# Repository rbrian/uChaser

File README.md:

# uFollow
Follow the project here: https://hackaday.io/project/190427-uchaser-ultrasonic-following-control-system

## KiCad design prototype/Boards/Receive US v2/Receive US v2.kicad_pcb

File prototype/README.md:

Prototype receiver and transmitter:

Transmitter firmware Todo list:
- [ ] Refactor to align with receiver code structure
- [x] JSON storage for settings
- [x] Automatic pairing with receiver (initiated by receiver)
- [ ] Add webserver, wifi access point
- [ ] Create a configuration page
- [ ] Implement the LED
- [ ] Remove the display or make it optional (use the qwiic connector)
- [ ] Get rid of all the serial.print commands everwhere
- [ ] Enable/disable, to stop the receiver from outputting

Receiver firmware todo list:
- [x] Add webserver, wifi access point
- [x] JSON storage for settings
- [x] Automatic pairing - one button
- [ ] Create a configuration page
- [ ] Make the LED do more interesting stuff
- [ ] Remove the display or make it optional (use the qwiic connector)
- [ ] Get rid of all the serial.print commands everwhere
- [ ] Outputs: UART, PWM, I2C, SPI, etc?
- [ ] Enable/Disable from transmitter
- [ ] Improve the averaging/smoothing.  Throw out bogus values
- [ ] Handle signal loss or line of sight issues
- [ ] Measure the jitter in ESP-NOW timing

Hardware wish list:
- [x] Next revision of receiver board
- [ ] Receiver mcu board: clearly mark TX and RX as IN or OUT
- [ ] Receiver mcu board: SCL and SDA are swapped
- [ ] Receiver mcu board: replace the diode with a mosfet
- [ ] Power supply for transmitter suitable for battery operation
- [ ] Try out switching between multiple tx transcievers for better angle tolerance
- [ ] Figure out which pins to expose

There are two main layers - RF and Ultrasonic.  The RF layer is wifi, using the ESP-NOW protocol.  The transmitting device sends a packet and the receiving one receives it (duh).

We are using the ESP32-S3 devkit board: https://docs.espressif.com/projects/esp-idf/en/latest/esp32s3/hw-reference/esp32s3/user-guide-devkitc-1.html
and this adafruit OLED display: https://www.adafruit.com/product/4650

For now the circuits are identical, only the code is different.

RMT peripheral documentation (for generating waveforms/pulse sequences)
https://docs.espressif.com/projects/esp-idf/en/latest/esp32s3/api-reference/peripherals/rmt.html

For the revision 1 receiver:
- The squelch pin mutes the data output while it is high
- The data pin is normally low, transitions to high when a ping is received
- The squelch pin also resets the one-shot circuit, so:
1. Keep the squelch pin high normally
2. When a wifi packet is received, set that pin to low
3. When the data pin goes high (interrupt pin), log that timestamp and reset the squelch pin to high again
4. if too much time passes without the data pin changing, set the squelch high and wait for the next packet
5. Repeat forever

Component notes:
ESP32-S3 (this is the lowest model): https://www.lcsc.com/product-detail/WiFi-Modules_Espressif-Systems-ESP32-S3-WROOM-1-N4_C2913197.html

USB-UART CH340c: https://www.lcsc.com/product-detail/USB-ICs_WCH-Jiangsu-Qin-Heng-CH340C_C84681.html

DC-DC Module: https://www.lcsc.com/product-detail/Power-Modules_DEXU-Electronics-K7803M-1000R3_C2916516.html

almost 12 inch cable with JST XH connector: https://www.lcsc.com/product-detail/Dupont-Cable-Terminal-Block-Cable-Electronic-Cable_DEALON-LNN254-100724-300-4P_C5160861.html

Same cable but double ended: https://www.lcsc.com/product-detail/Dupont-Cable-Terminal-Block-Cable-Electronic-Cable_DEALON-LDS254-100724-300-4P_C5160865.html

XH vertical board connector:
- white: https://www.lcsc.com/product-detail/Wire-To-Board-Wire-To-Wire-Connector_HCTL-XH-4A_C2908602.html
- black: https://www.lcsc.com/product-detail/Wire-To-Board-Wire-To-Wire-Connector_HCTL-XH-4A-B_C2979570.html
- red: https://www.lcsc.com/product-detail/Wire-To-Board-Wire-To-Wire-Connector_HCTL-XH-4A-R_C2979568.html
- blue: https://www.lcsc.com/product-detail/Wire-To-Board-Wire-To-Wire-Connector_HCTL-XH-4A-L_C2979569.html

XH horizontal board connector: https://www.lcsc.com/product-detail/Wire-To-Board-Wire-To-Wire-Connector_BOOMELE-Boom-Precision-Elec-XH-4AW_C21273.html

Qwiic
- Real JST: https://www.lcsc.com/product-detail/Wire-To-Board-Wire-To-Wire-Connector_JST-Sales-America-BM04B-SRSS-TB-LF-SN_C160390.html
- Cheap clone: https://www.lcsc.com/product-detail/Wire-To-Board-Wire-To-Wire-Connector_JUSHUO-AFC10-S04QCA-00_C2764183.html

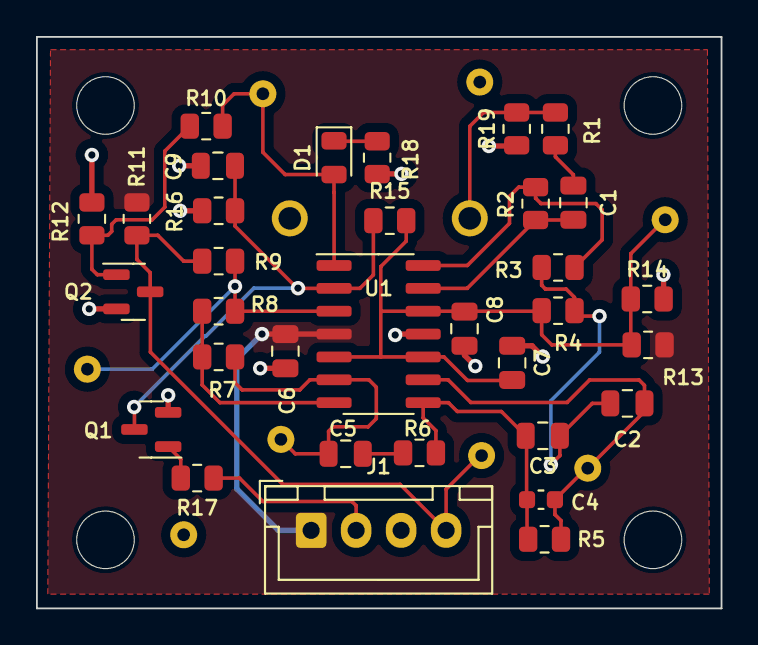
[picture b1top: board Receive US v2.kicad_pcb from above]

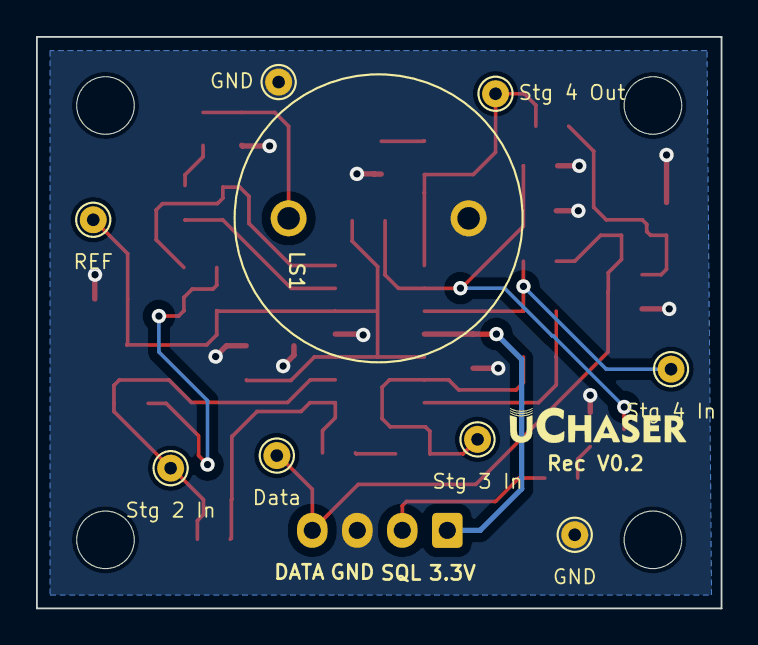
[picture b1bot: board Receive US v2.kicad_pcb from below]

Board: 2 copper layers, 38.0 x 31.7 mm, 47 parts (10 on the bottom side), 21 nets.

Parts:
C1, C5: 10nF; C_0805_2012Metric
C2, C3, C7, C9: 1nF; C_0805_2012Metric
C4: 68pF; C_0603_1608Metric
C6, C8: 1uF; C_0805_2012Metric
D1: LED; LED_0805_2012Metric
H1, H2, H3, H4: MountingHole; MountingHole_3.2mm_M3
J1: Conn_01x04_Socket; JST_XH_B4B-XH-A_1x04_P2.50mm_Vertical
LS1: Speaker_Ultrasound; ULTRASONIC_16MM
Logo1: logo
Q1, Q2: MMBT3904; SOT-23
R1, R6, R10, R13, R14, R17: 10K; R_0805_2012Metric
R2, R5, R7: 75K; R_0805_2012Metric
R3: 6.8K; R_0805_2012Metric
R4: 220; R_0805_2012Metric
R8: 4.3K; R_0805_2012Metric
R9, R15: 120K; R_0805_2012Metric
R11: 1K; R_0805_2012Metric
R12: 3.9K; R_0805_2012Metric
R16: 2M; R_0805_2012Metric
R18: 100; R_0805_2012Metric
R19: DO NOT POPULATE; R_0805_2012Metric
TP1, TP2, TP3, TP4, TP5, TP6, TP7, TP8: TestPoint; TestPoint_THTPad_D1.5mm_Drill0.7mm
U1: LM324; SOIC-14_3.9x8.7mm_P1.27mm

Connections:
+3.3V: C6.2, J1.1, R11.2, R13.2, U1.4 (V+)
/DATA: J1.4, Q2.3 (C), R9.2, R11.1, TP8.1
/SQUELCH: J1.2, R17.1
GND: C6.1, C7.1, C8.1, C9.1, J1.3, LS1.2, Q1.2 (E), Q2.2 (E), R12.1, R14.2, R16.2, R18.1, R19.1, TP1.1, TP2.1, U1.11 (V-)
unnamed: C1.1, R1.2
unnamed: C2.1, C3.1, R3.2, R4.2
unnamed: C3.2, C4.2, R5.2, R6.1, U1.8
unnamed: C5.1, R6.2
unnamed: D1.2 (A), R10.1, TP7.1, U1.1
unnamed: D1.1 (K), R18.2
unnamed: LS1.1, R1.1, R19.2
unnamed: Q1.1 (B), R17.2
unnamed: C9.2, Q1.3 (C), R15.1, R16.1, U1.2 (-)
unnamed: Q2.1 (B), R10.2, R12.2
unnamed: R2.2, R3.1, U1.14
unnamed: R7.2, R8.1, U1.7
unnamed: R8.2, R9.1, TP6.1, U1.3 (+)
unnamed: C7.2, C8.2, R4.1, R13.1, R14.1, R15.2, TP4.1, U1.5 (+), U1.10 (+), U1.12 (+)
unnamed: C5.2, R7.1, TP5.1, U1.6 (-)
unnamed: C2.2, C4.1, R5.1, TP3.1, U1.9 (-)
unnamed: C1.2, R2.1, U1.13 (-)

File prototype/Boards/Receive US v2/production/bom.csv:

Designator,Footprint,Quantity,Value,LCSC Part #
"C1, C5",0805,2,10nF,C1710
"C2, C3, C7, C9",0805,4,1nF,C46653
C4,0603,1,68pF,C28262
"C6, C8",0805,2,1uF,C28323
D1,0805,1,LED,C84256
"H1, H2, H3, H4",MountingHole_3.2mm_M3,4,MountingHole,
J1,JST_XH_B4B-XH-A_1x04_P2.50mm_Vertical,1,Conn_01x04_Socket,
LS1,ULTRASONIC_16MM,1,Speaker_Ultrasound,
"Q1, Q2",SOT-23,2,MMBT3904,C20526
"R1, R10, R13, R14, R17, R6",0805,6,10K,C17414
R11,0805,1,1K,C17513
R12,0805,1,3.9K,C17614
"R15, R9",0805,2,120K,C17436
R16,0805,1,2M,C26112
R18,0805,1,100,C17408
R19,0805,1,DO NOT POPULATE,
"R2, R5, R7",0805,3,75K,C17819
R3,0805,1,6.8K,C17772
R4,0805,1,220,C17557
R8,0805,1,4.3K,C17667
"TP1, TP2, TP3, TP4, TP5, TP6, TP7, TP8",TestPoint_THTPad_D1.5mm_Drill0.7mm,8,TestPoint,
U1,SOIC-14_3.9x8.7mm_P1.27mm,1,LM324,C71035

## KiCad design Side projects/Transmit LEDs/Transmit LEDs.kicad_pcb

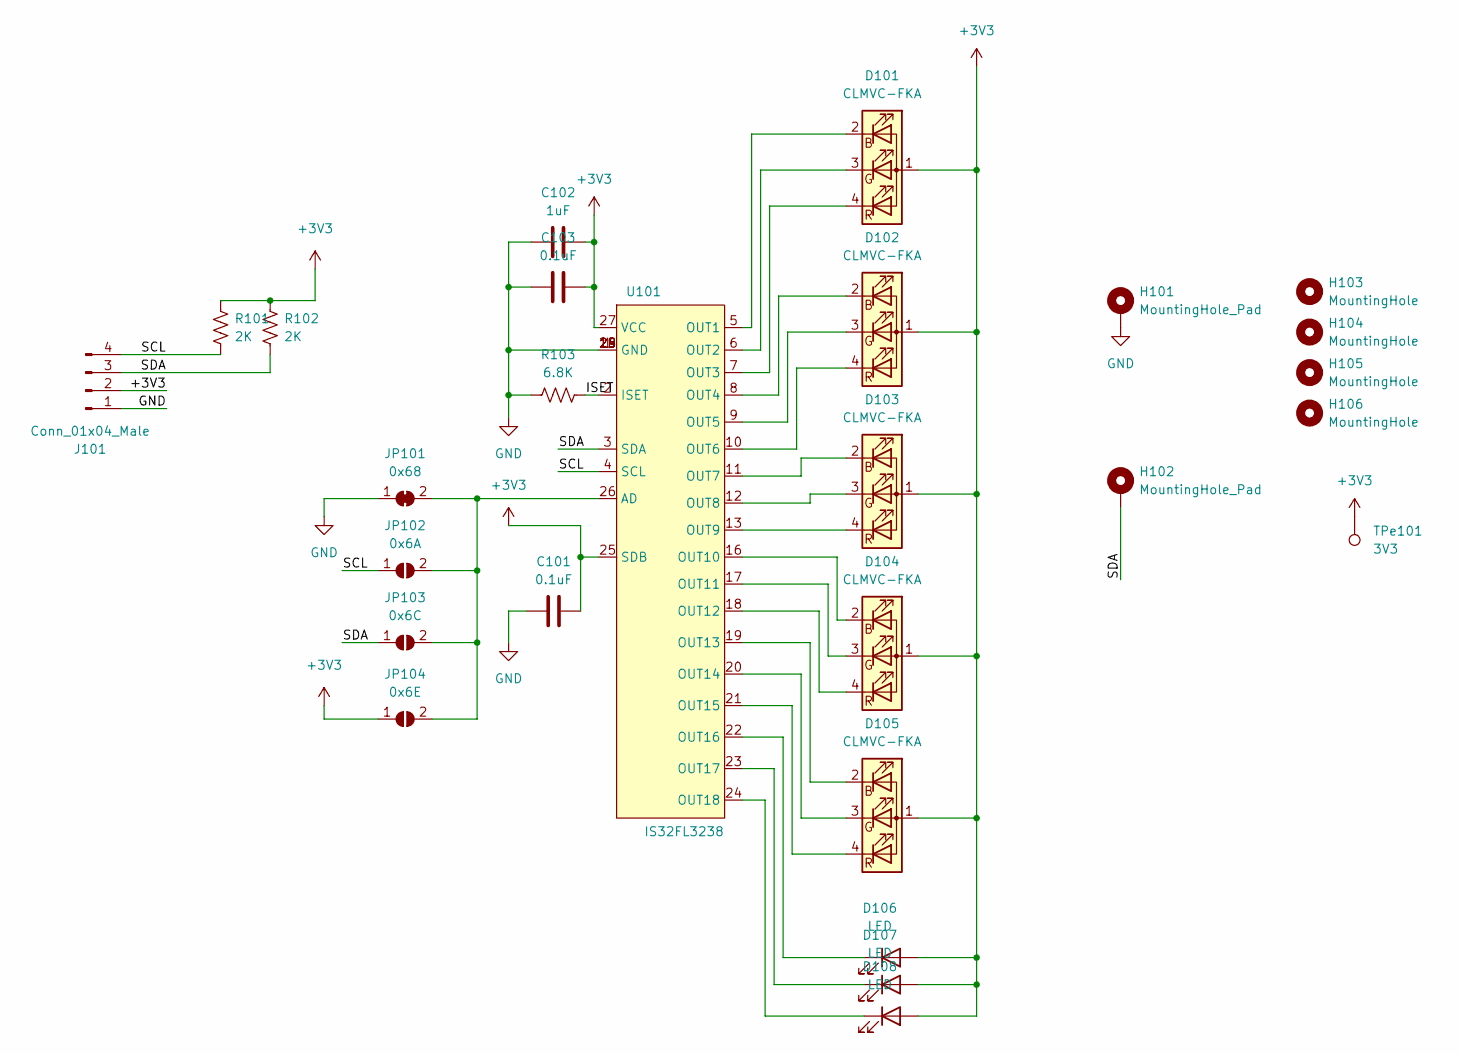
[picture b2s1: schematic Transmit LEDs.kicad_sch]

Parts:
C101, C103: 0.1uF; C_0805_2012Metric_Pad1.18x1.45mm_HandSolder
C102: 1uF; C_0805_2012Metric_Pad1.18x1.45mm_HandSolder
D101, D102, D103, D104, D105: CLMVC-FKA; LED_Cree-PLCC4_2x2mm_CW
D106, D107, D108: LED; LED_0805_2012Metric_Pad1.15x1.40mm_HandSolder
H101, H102: MountingHole_Pad; MountingHole_2.2mm_M2_DIN965_Pad_TopBottom
H103, H104, H105, H106: MountingHole; MountingHole_2.2mm_M2
J101: Conn_01x04_Male; JST_SH_SM04B-SRSS-TB_1x04-1MP_P1.00mm_Horizontal
JP101: 0x68; SolderJumper-2_P1.3mm_Bridged_RoundedPad1.0x1.5mm
JP102: 0x6A; SolderJumper-2_P1.3mm_Open_RoundedPad1.0x1.5mm
JP103: 0x6C; SolderJumper-2_P1.3mm_Open_RoundedPad1.0x1.5mm
JP104: 0x6E; SolderJumper-2_P1.3mm_Open_RoundedPad1.0x1.5mm
R101, R102: 2K; R_0805_2012Metric_Pad1.20x1.40mm_HandSolder
R103: 6.8K; R_0805_2012Metric_Pad1.20x1.40mm_HandSolder
TPe101: 3V3; TestPoint_Pad_D2.0mm
U101: IS32FL3238; TSSOP-28-1EP_4.4x9.7mm_P0.65mm_EP2.85x6.7mmVias

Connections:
+3V3: C101.1, C102.1, C103.1, D101.1 (A), D102.1 (A), D103.1 (A), D104.1 (A), D105.1 (A), D106.2 (A), D107.2 (A), D108.2 (A), J101.2, JP104.1 (A), R101.2, R102.2, TPe101.1, U101.25 (SDB), U101.27 (VCC)
/ISET: R103.2, U101.2 (ISET)
/SCL: J101.4, JP102.1 (A), R101.1, U101.4 (SCL)
/SDA: H102.1, J101.3, JP103.1 (A), R102.1, U101.3 (SDA)
GND: C101.2, C102.2, C103.2, H101.1, J101.1, JP101.1 (A), R103.1, U101.1 (GND), U101.14 (GND), U101.15 (GND), U101.28 (GND), U101.29 (GND)
unnamed: D101.2 (BK), U101.5 (OUT1)
unnamed: D101.3 (GK), U101.6 (OUT2)
unnamed: D101.4 (RK), U101.7 (OUT3)
unnamed: D102.2 (BK), U101.8 (OUT4)
unnamed: D102.3 (GK), U101.9 (OUT5)
unnamed: D102.4 (RK), U101.10 (OUT6)
unnamed: D103.2 (BK), U101.11 (OUT7)
unnamed: D103.3 (GK), U101.12 (OUT8)
unnamed: D103.4 (RK), U101.13 (OUT9)
unnamed: D104.2 (BK), U101.16 (OUT10)
unnamed: D104.3 (GK), U101.17 (OUT11)
unnamed: D104.4 (RK), U101.18 (OUT12)
unnamed: D105.2 (BK), U101.19 (OUT13)
unnamed: D105.3 (GK), U101.20 (OUT14)
unnamed: D105.4 (RK), U101.21 (OUT15)
unnamed: D106.1 (K), U101.22 (OUT16)
unnamed: D107.1 (K), U101.23 (OUT17)
unnamed: D108.1 (K), U101.24 (OUT18)
unnamed: JP101.2 (B), JP102.2 (B), JP103.2 (B), JP104.2 (B), U101.26 (AD)

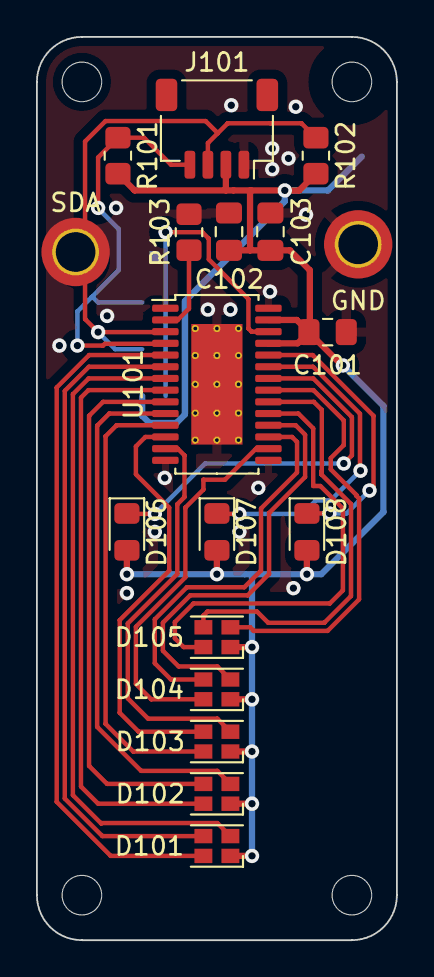
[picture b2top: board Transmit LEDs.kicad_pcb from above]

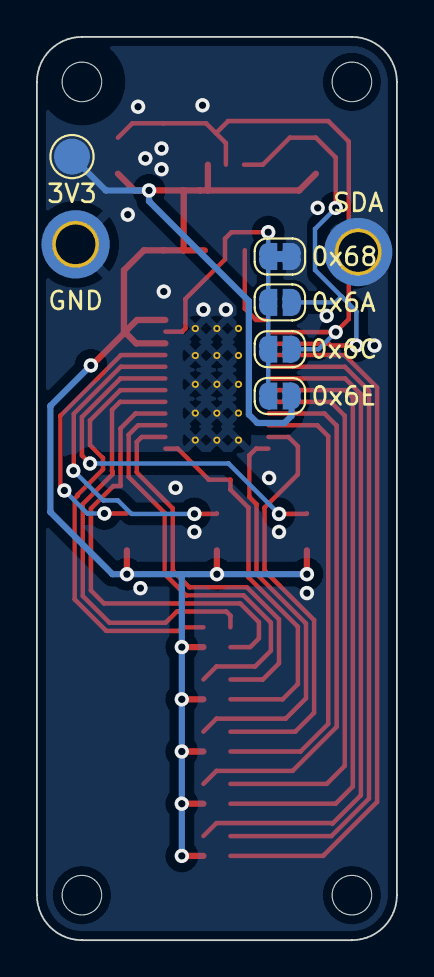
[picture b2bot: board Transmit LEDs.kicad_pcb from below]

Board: 2 copper layers, 20.0 x 50.2 mm, 27 parts (5 on the bottom side), 24 nets.

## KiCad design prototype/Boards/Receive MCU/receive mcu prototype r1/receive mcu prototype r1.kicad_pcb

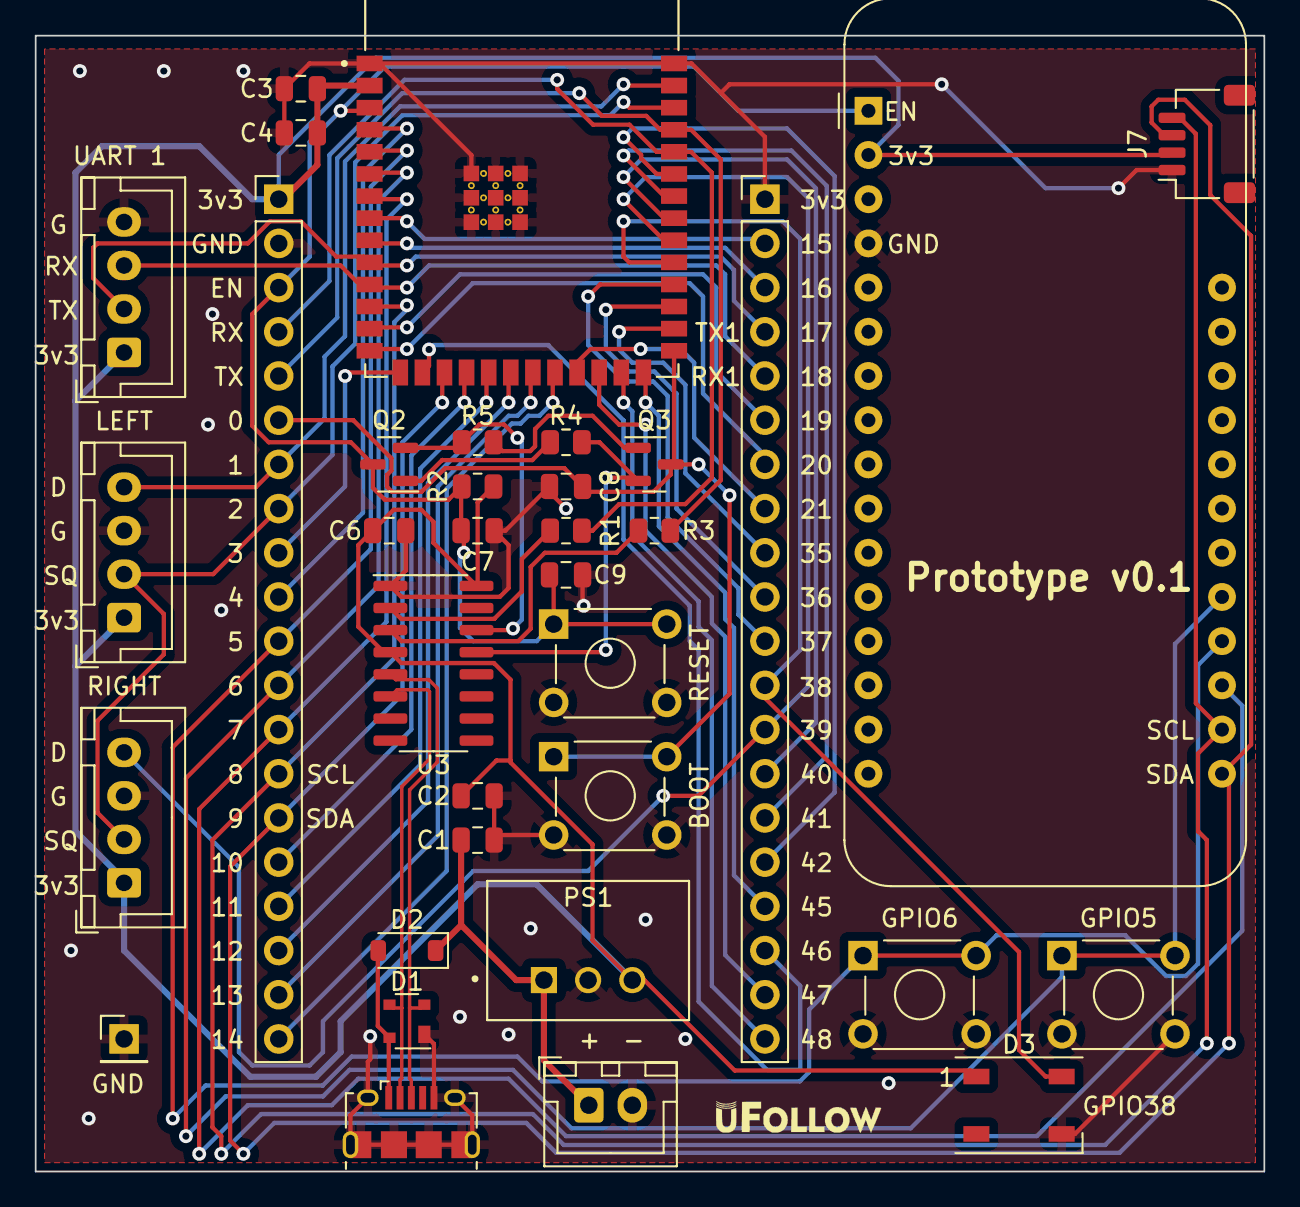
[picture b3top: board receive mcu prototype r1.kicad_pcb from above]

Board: 2 copper layers, 70.6 x 65.3 mm, 36 parts (0 on the bottom side), 49 nets.

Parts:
C1, C3: 10uF; C_0805_2012Metric
C2: 22uF; C_0805_2012Metric
C4, C6, C8, C9: .1uF; C_0805_2012Metric
C7: 1uF; C_0805_2012Metric
D1: PRTR5V0U2X; SOT-143
D2: D; D_SOD-123
D3: WS2812B; LED_WS2812B_PLCC4_5.0x5.0mm_P3.2mm
J1, J2, J11: Conn_01x04_Socket; JST_XH_B4B-XH-A_1x04_P2.50mm_Vertical
J3: Conn_01x02_Socket; JST_XH_B2B-XH-A_1x02_P2.50mm_Vertical
J4: USB_B_Micro; USB_Micro-B_Amphenol_10118194_Horizontal
J5, J6: Conn_01x20_Pin; PinHeader_1x20_P2.54mm_Vertical
J7: Conn_01x04_Socket; JST_SH_SM04B-SRSS-TB_1x04-1MP_P1.00mm_Horizontal
Logo1: uFollowLogo
PS1: K7803M-1000R3; CONV_K7803M-1000R3
Q2, Q3: Q_NPN_BEC; SOT-23
R1, R3: 2.4K; R_0805_2012Metric
R2, R4, R5: 10K; R_0805_2012Metric
SW1, SW2, SW3, SW4: SW_Push; SW_TH_Tactile_Omron_B3F-10xx
TP1: TestPoint; PinHeader_1x01_P2.54mm_Vertical
U1: ESP32-S3-WROOM-1-N4R2; XCVR_ESP32-S3-WROOM-1-N4R2
U2: Adafruit_Feather
U3: CH340C; SOIC-16_3.9x9.9mm_P1.27mm

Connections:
+3.3V: C2.1, C3.1, C4.1, C6.1, D3.1 (VDD), J1.1, J2.1, J6.1, J7.2, J11.1, PS1.3 (+VO), R2.2, U1.2 (3V3), U2.2 (3v3), U3.4 (V3), U3.16 (VCC)
/EN: C7.1, C9.1, J6.3, Q2.3 (C), R2.1, SW1.1, U1.3 (EN), U2.1 (RST)
/GPIO0: C8.1, J6.6, Q3.3 (C), SW2.1, U1.27 (IO0)
/GPIO1: J1.4, J6.7, U1.39 (IO1)
/GPIO2: J1.2, J2.2, J6.8, U1.38 (IO2)
/GPIO3: J6.9, U1.15 (IO3)
/GPIO4: J6.10, U1.4 (IO4)
/GPIO5: J6.11, SW3.1, U1.5 (IO5), U2.20 (B)
/GPIO6: J6.12, SW4.1, U1.6 (IO6), U2.21 (C)
/GPIO7: J6.13, U1.7 (IO7), U2.19 (A)
/GPIO8: J6.14, J7.4, U1.12 (IO8), U2.18 (SCL)
/GPIO9: J6.15, J7.3, U1.17 (IO9), U2.17 (SDA)
/GPIO10: J6.16, U1.18 (IO10)
/GPIO11: J6.17, U1.19 (IO11)
/GPIO12: J6.18, U1.20 (IO12)
/GPIO13: J6.19, U1.21 (IO13)
/GPIO14: J6.20, U1.22 (IO14)
/GPIO15: J5.2, U1.8 (IO15)
/GPIO16: J5.3, U1.9 (IO16)
/GPIO17/TX1: J5.4, J11.2, U1.10 (IO17)
/GPIO18/RX1: J5.5, J11.3, U1.11 (IO18)
/GPIO19: J5.6, U1.13 (IO19)
/GPIO20: J5.7, U1.14 (IO20)
/GPIO21: J5.8, U1.23 (IO21)
/GPIO35: J5.9, U1.28 (IO35)
/GPIO36: J5.10, U1.29 (IO36)
/GPIO37: J5.11, U1.30 (IO37)
/GPIO38: D3.4 (DIN), J5.12, U1.31 (IO38)
/GPIO39: J2.4, J5.13, U1.32 (IO39)
/GPIO40: J5.14, U1.33 (IO40)
/GPIO41: J5.15, U1.34 (IO41)
/GPIO42: J5.16, U1.35 (IO42)
/GPIO45: J5.17, U1.26 (IO45)
/GPIO46: J5.18, U1.16 (IO46)
/GPIO47: J5.19, U1.24 (IO47)
/GPIO48: J5.20, U1.25 (IO48)
/RX: J6.4, R1.2, U1.36 (RXD0)
/TX: J6.5, R3.2, U1.37 (TXD0)
/usb/D+: D1.2 (I/O1), J4.3 (D+), U3.5 (UD+)
/usb/D-: D1.3 (I/O2), J4.2 (D-), U3.6 (UD-)
/usb/DTR: Q3.2 (E), R4.1, U3.13 (~DTR)
/usb/RTS: Q2.2 (E), R5.1, U3.14 (~RTS)
GND: C1.2, C2.2, C3.2, C4.2, C6.2, C7.2, C8.2, C9.2, D1.1 (GND), D3.3 (VSS), J1.3, J2.3, J3.2, J4.5 (GND), J4.6 (Shield), J5.1, J6.2, J7.1, J11.4, PS1.2 (GND), SW1.2, SW2.2, SW3.2, SW4.2, TP1.1, U1.1 (GND), U1.40 (GND), U1.41_2 (GND), U1.41_3 (GND), U1.41_4 (GND), U1.41_5 (GND), U1.41_6 (GND), U1.41_7 (GND), U1.41_8 (GND), U1.41_9 (GND), U2.4 (GND), U3.1 (GND)
unnamed: D1.4 (VCC), D2.2 (A), J4.1 (VBUS)
unnamed: Q2.1 (B), R4.2
unnamed: Q3.1 (B), R5.2
unnamed: R3.1, U3.3 (RXD)
unnamed: R1.1, U3.2 (TXD)
VCC: C1.1, D2.1 (K), J3.1, PS1.1 (VIN)

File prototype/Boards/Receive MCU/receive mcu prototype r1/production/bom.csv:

Designator,Footprint,Quantity,Value,LCSC Part #
"C1, C3",0805,2,10uF,
C2,0805,1,22uF,
"C4, C6, C8, C9",0805,4,.1uF,
C7,0805,1,1uF,
D1,SOT-143,1,PRTR5V0U2X,C2827688
D2,D_SOD-123,1,D,C64898
D3,LED_WS2812B_PLCC4_5.0x5.0mm_P3.2mm,1,WS2812B,
"J1, J11, J2",JST_XH_B4B-XH-A_1x04_P2.50mm_Vertical,3,Conn_01x04_Socket,
J3,JST_XH_B2B-XH-A_1x02_P2.50mm_Vertical,1,Conn_01x02_Socket,
J4,USB_Micro-B_Amphenol_10118194_Horizontal,1,USB_B_Micro,C132563
"J5, J6",PinHeader_1x20_P2.54mm_Vertical,2,Conn_01x20_Pin,
J7,JST_SH_SM04B-SRSS-TB_1x04-1MP_P1.00mm_Horizontal,1,Conn_01x04_Socket,
PS1,CONV_K7803M-1000R3,1,K7803M-1000R3,
"Q2, Q3",SOT-23,2,Q_NPN_BEC,C20526
"R1, R3",0805,2,2.4K,C17526
"R2, R4, R5",0805,3,10K,C17414
"SW1, SW2, SW3, SW4",SW_TH_Tactile_Omron_B3F-10xx,4,SW_Push,
TP1,PinHeader_1x01_P2.54mm_Vertical,1,TestPoint,
U1,XCVR_ESP32-S3-WROOM-1-N4R2,1,ESP32-S3-WROOM-1-N4R2,
U2,Adafruit_Feather,1,~,
U3,SOIC-16_3.9x9.9mm_P1.27mm,1,CH340C, C84681

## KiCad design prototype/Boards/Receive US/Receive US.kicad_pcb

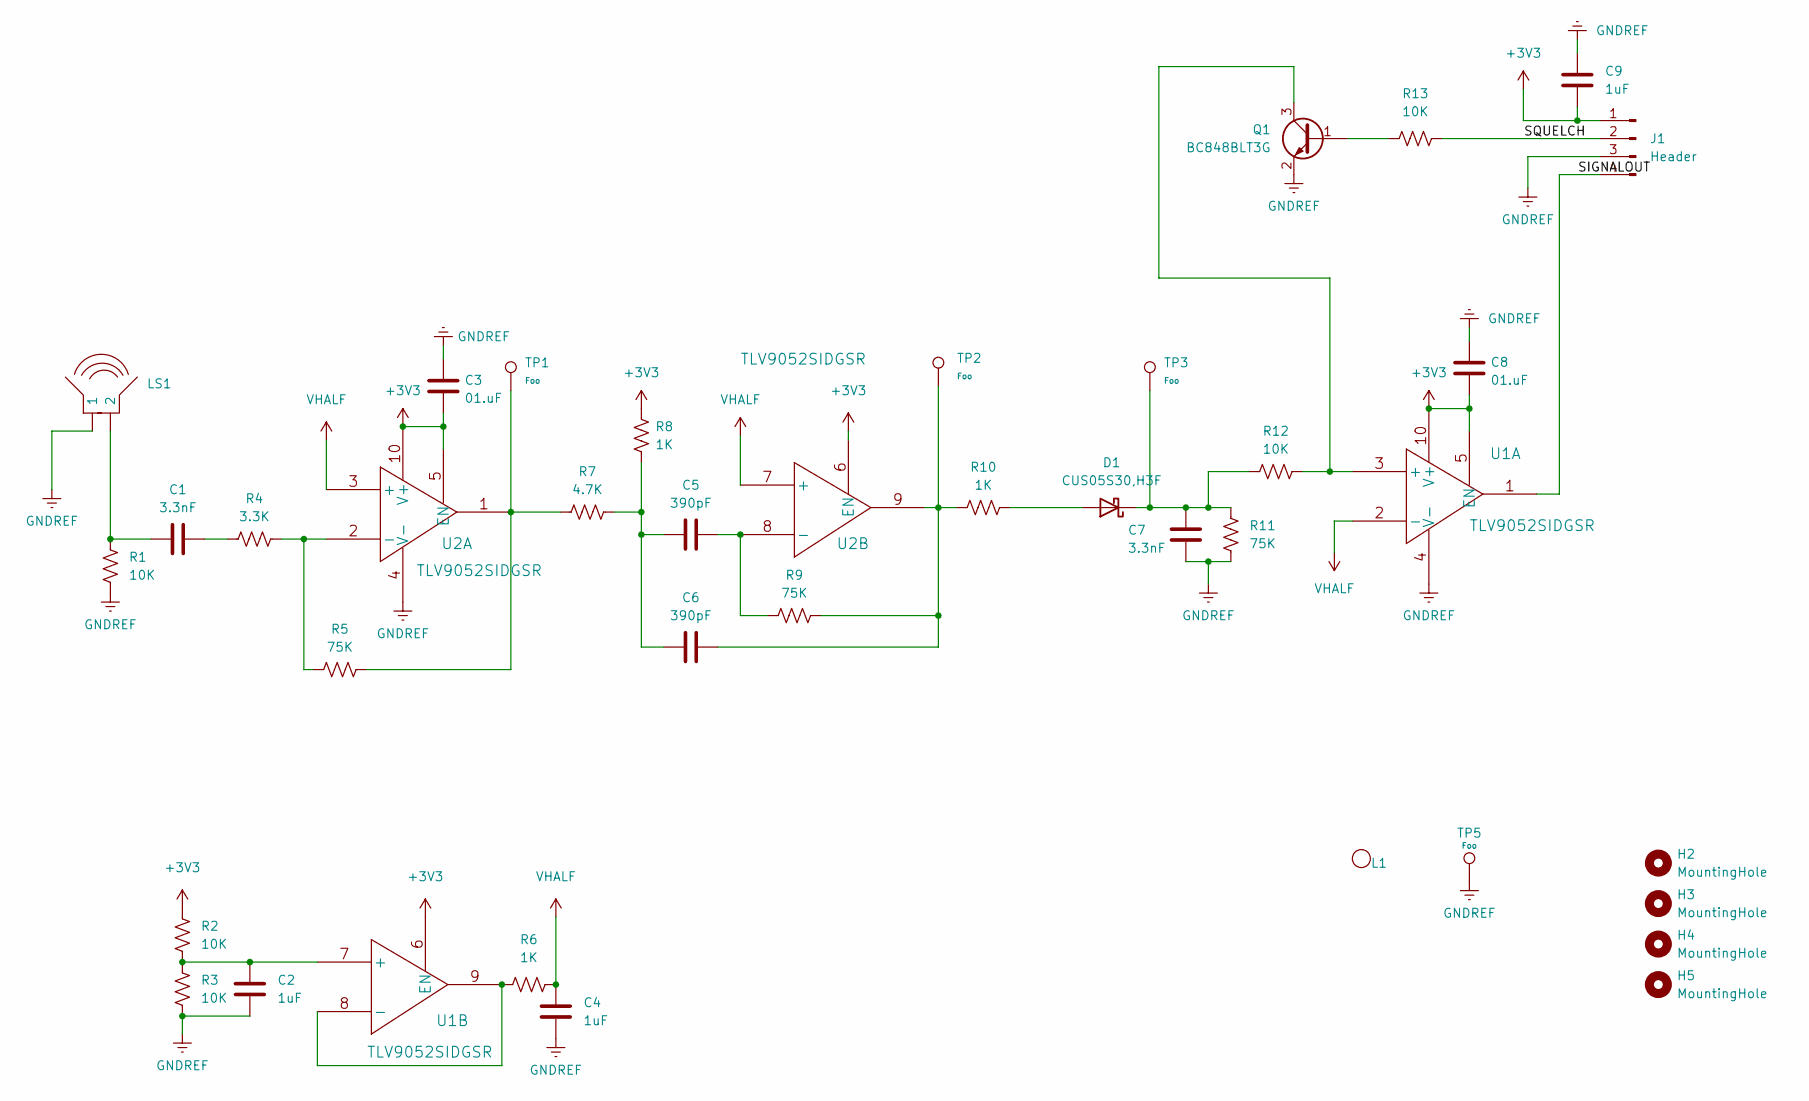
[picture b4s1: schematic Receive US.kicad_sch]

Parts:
C1, C7: 3.3nF; C_0603_1608Metric_Pad1.08x0.95mm_HandSolder; MFG PN CL10B332KB8NNNC
C2, C4, C9: 1uF; C_0603_1608Metric_Pad1.08x0.95mm_HandSolder; MFG PN CL10A105KA8NNNC
C3, C8: 01.uF; C_0603_1608Metric_Pad1.08x0.95mm_HandSolder; MFG PN TMK107BJ104KA-T
C5, C6: 390pF; C_0603_1608Metric_Pad1.08x0.95mm_HandSolder; MFG PN CL10B391KB8NNNC
D1: CUS05S30,H3F; D_SOD-323_HandSoldering; MFG PN CUS05S30,H3F
H2, H3, H4, H5: MountingHole; MountingHole_3.2mm_M3
J1: Header; PinHeader_1x04_P2.54mm_Vertical
L1: uFollowLogo
LS1: USTransducer; ULTRASONIC_16MM
Q1: BC848BLT3G; SOT-23; MFG PN BC848BLT3G
R1, R2, R3, R12, R13: 10K; R_0603_1608Metric_Pad0.98x0.95mm_HandSolder; MFG PN RC0603FR-1310KL
R4: 3.3K; R_0603_1608Metric_Pad0.98x0.95mm_HandSolder; MFG PN RC0603FR-103K3L
R5, R9, R11: 75K; R_0603_1608Metric_Pad0.98x0.95mm_HandSolder; MFG PN RC0603FR-1075KL
R6, R8, R10: 1K; R_0603_1608Metric_Pad0.98x0.95mm_HandSolder; MFG PN RC0603FR-131KL
R7: 4.7K; R_0603_1608Metric_Pad0.98x0.95mm_HandSolder; MFG PN RC0603FR-134K7L
TP1, TP2, TP3, TP5: TestPoint; TestPoint_Keystone_5005-5009_Compact; MFG PN 1041
U1, U2: TLV9052SIDGSR; TLV9002SIDGSR; MFG PN TLV9052SIDGSR

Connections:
+3V3: C3.1, C8.1, C9.1, J1.1, R2.2, R8.1, U1.5 (EN), U1.6 (EN), U1.10 (V+), U2.5 (EN), U2.6 (EN), U2.10 (V+)
/SIGNALOUT: J1.4, U1.1
/SQUELCH: J1.2, R13.2
GNDREF: C2.1, C3.2, C4.1, C7.1, C8.2, C9.2, J1.3, LS1.1, Q1.2 (E), R1.1, R3.1, R11.1, TP5.1, U1.4 (V-), U2.4 (V-)
unnamed: C1.1, LS1.2, R1.2
unnamed: C1.2, R4.1
unnamed: C5.1, C6.1, R7.2, R8.2
unnamed: C6.2, R9.2, R10.1, TP2.1, U2.9
unnamed: D1.2 (A), R10.2
unnamed: C7.2, D1.1 (K), R11.2, R12.1, TP3.1
unnamed: Q1.1 (B), R13.1
unnamed: Q1.3 (C), R12.2, U1.3 (+)
unnamed: R5.2, R7.1, TP1.1, U2.1
unnamed: C2.2, R2.1, R3.2, U1.7 (+)
unnamed: R6.2, U1.8 (-), U1.9
unnamed: R4.2, R5.1, U2.2 (-)
unnamed: C5.2, R9.1, U2.8 (-)
VHALF: C4.2, R6.1, U1.2 (-), U2.3 (+), U2.7 (+)

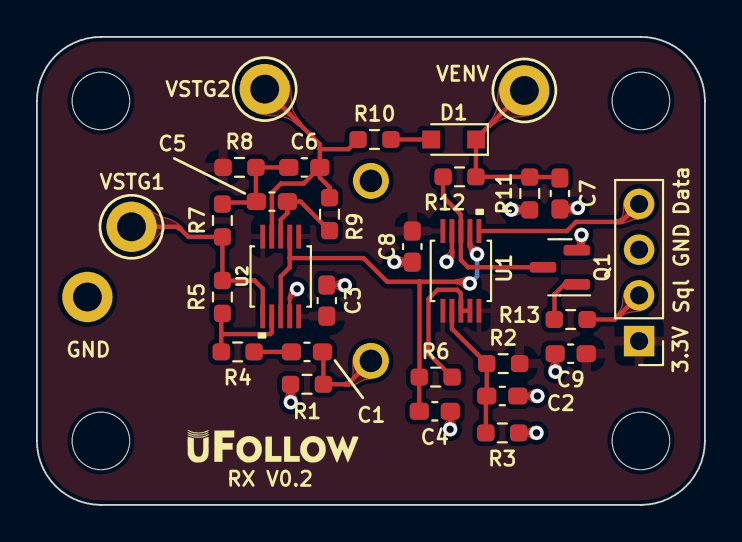
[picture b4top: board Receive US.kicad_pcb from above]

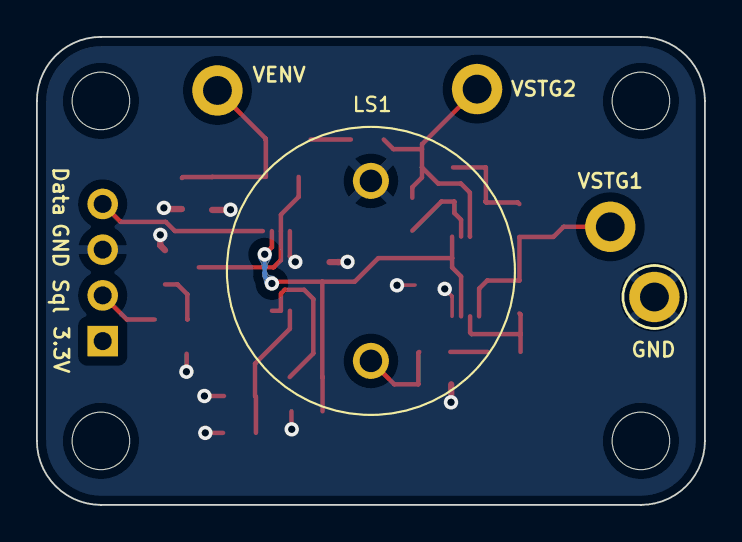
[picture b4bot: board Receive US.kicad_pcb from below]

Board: 2 copper layers, 37.1 x 26.0 mm, 37 parts (2 on the bottom side), 18 nets.

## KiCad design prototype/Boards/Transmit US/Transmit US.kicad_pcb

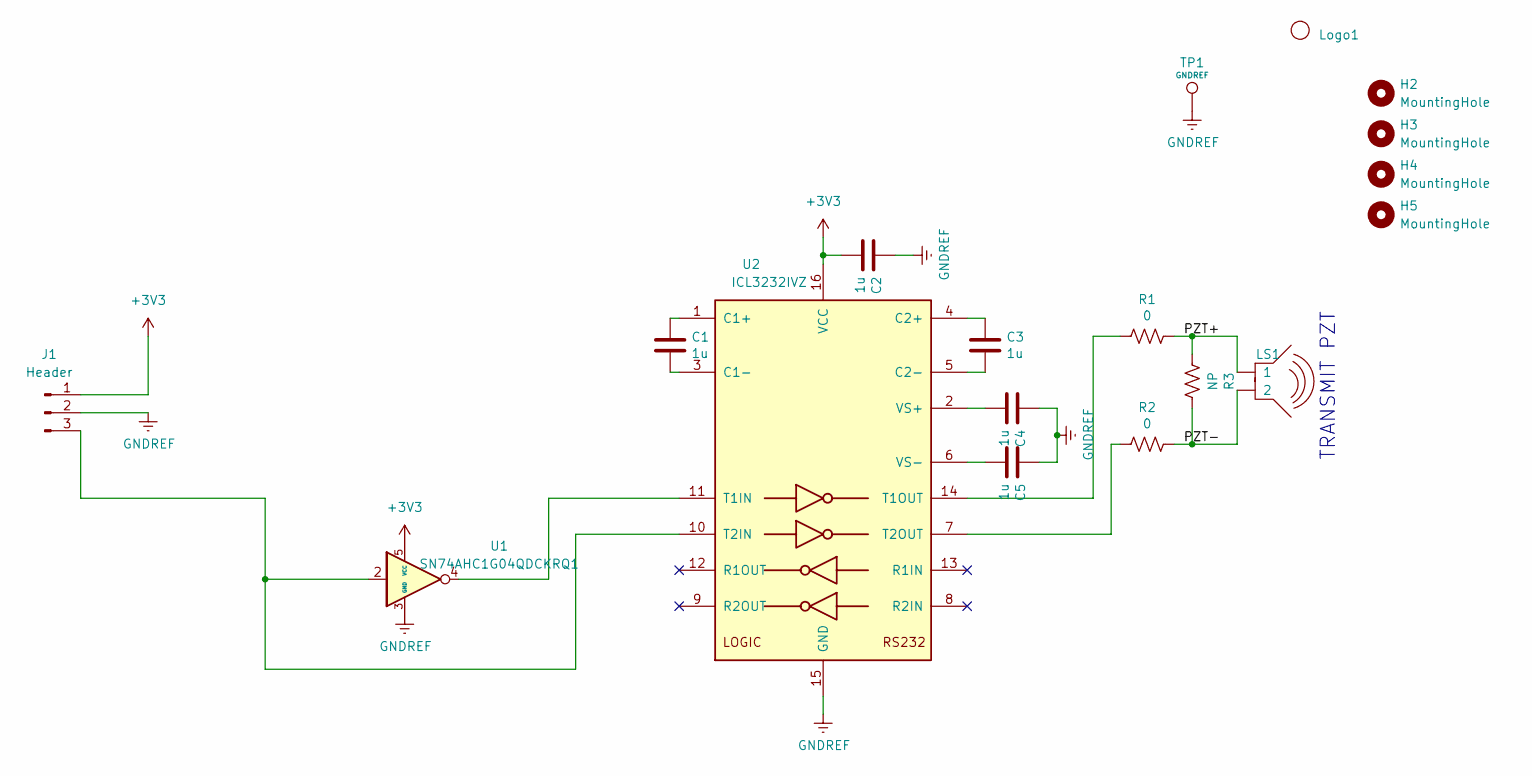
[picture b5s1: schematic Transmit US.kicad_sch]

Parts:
C1, C2, C3, C4, C5: 1u; C_0603_1608Metric_Pad1.08x0.95mm_HandSolder; MFG PN CL10A105KA8NNNC
H2, H3, H4, H5: MountingHole; MountingHole_3.2mm_M3
J1: Header; PinHeader_1x03_P2.54mm_Vertical
LS1: USTransducer; ULTRASONIC_16MM
Logo1: uFollowLogo
R1, R2: 0; R_0603_1608Metric_Pad0.98x0.95mm_HandSolder; MFG PN RC0603FR-070RL
R3: NP; R_0603_1608Metric_Pad0.98x0.95mm_HandSolder; MFG PN NA
TP1: TestPoint; TestPoint_Keystone_5005-5009_Compact; MFG PN 1041
U1: SN74AHC1G04QDCKRQ1; SOT-353_SC-70-5_Handsoldering; MFG PN SN74AHC1G04QDCKRQ1
U2: ICL3232IVZ; TSSOP-16_4.4x5mm_P0.65mm; MFG PN ICL3232IVZ

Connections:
+3V3: C2.1, J1.1, U1.5 (VCC), U2.16 (VCC)
/PZT+: LS1.1, R1.2, R3.2
/PZT-: LS1.2, R2.2, R3.1
GNDREF: C2.2, C4.2, C5.2, J1.2, TP1.1, U1.3 (GND), U2.15 (GND)
unnamed: J1.3, U1.2, U2.10 (T2IN)
unnamed: C1.2, U2.1 (C1+)
unnamed: C1.1, U2.3 (C1-)
unnamed: C3.2, U2.4 (C2+)
unnamed: C3.1, U2.5 (C2-)
unnamed: U1.4, U2.11 (T1IN)
unnamed: R1.1, U2.14 (T1OUT)
unnamed: R2.1, U2.7 (T2OUT)
unnamed: C4.1, U2.2 (VS+)
unnamed: C5.1, U2.6 (VS-)

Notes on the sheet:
TRANSMIT PZT

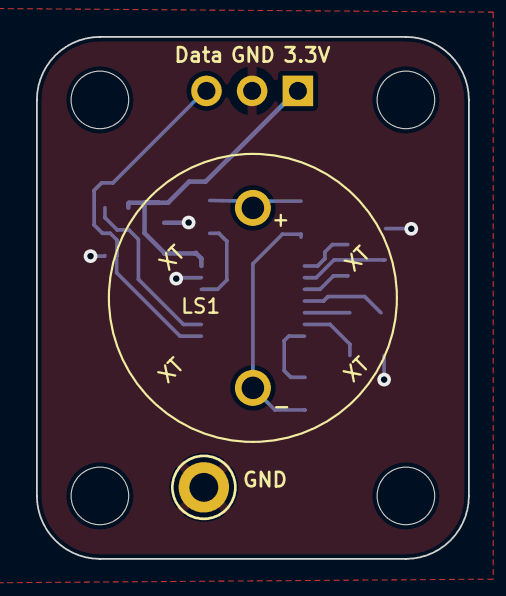
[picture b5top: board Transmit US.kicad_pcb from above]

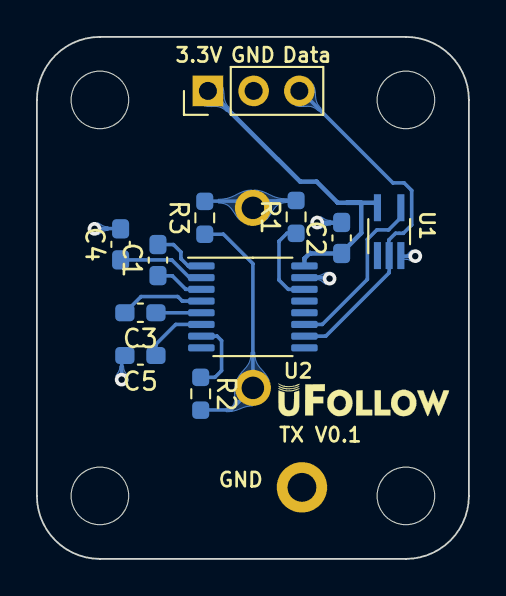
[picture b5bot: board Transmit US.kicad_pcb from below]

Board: 2 copper layers, 24.0 x 29.0 mm, 18 parts (12 on the bottom side), 14 nets.

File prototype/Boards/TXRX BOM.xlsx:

Source: | D:\Projects\Ultrasonic-Direction-Finder-Module\Boards\Transmit US\Transmit US.k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
Date: | 44691.877349537041
Tool: | Eeschema (6.0.2)
Generator: | C:\Program Files\KiCad\6.0\bin\scripting\plugins/bom_csv_grouped_by_value.py
Component Count: | 20
Individual Components:
Item | Qty | Reference(s) | Value | LibPart | Footprint | Datasheet | DK PN | MFG | MFG PN
 |  | C1 | 1u | Device:C | Capacitor_SMD:C_0603_1608Metric_Pad1.08x0.95mm_HandSolder | ~ | 478-1412-1-ND | AVX | 0805ZD105KAT2A
 |  | C2 | 1u | Device:C | Capacitor_SMD:C_0603_1608Metric_Pad1.08x0.95mm_HandSolder | ~ | 478-12799-1-ND | AVX | 0805ZD105KAT2A
 |  | C3 | 1u | Device:C | Capacitor_SMD:C_0603_1608Metric_Pad1.08x0.95mm_HandSolder | ~ | 478-1412-1-ND | AVX | 0805ZD104KAT2A
 |  | C4 | 1u | Device:C | Capacitor_SMD:C_0603_1608Metric_Pad1.08x0.95mm_HandSolder | ~ | 478-1412-1-ND | AVX | 0805ZD105KAT2A
 |  | C5 | 1u | Device:C | Capacitor_SMD:C_0603_1608Metric_Pad1.08x0.95mm_HandSolder | ~ | 478-1412-1-ND | AVX | 0805ZD105KAT2A
 |  | FID1 | Fiducial | Mechanical:Fiducial | Fiducial:Fiducial_1mm_Mask2mm | ~
 |  | FID2 | Fiducial | Mechanical:Fiducial | Fiducial:Fiducial_1mm_Mask2mm | ~
 |  | FID3 | Fiducial | Mechanical:Fiducial | Fiducial:Fiducial_1mm_Mask2mm | ~
 |  | H1 | GND | Mechanical:MountingHole_Pad | TestPoint:TestPoint_Keystone_5005-5009_Compact | ~
 |  | H2 | MountingHole | Mechanical:MountingHole | MountingHole:MountingHole_3.2mm_M3 | ~
 |  | H3 | MountingHole | Mechanical:MountingHole | MountingHole:MountingHole_3.2mm_M3 | ~
 |  | H4 | MountingHole | Mechanical:MountingHole | MountingHole:MountingHole_3.2mm_M3 | ~
 |  | H5 | MountingHole | Mechanical:MountingHole | MountingHole:MountingHole_3.2mm_M3 | ~
 |  | J1 | Phoenix 1984620 | Connector:Screw_Terminal_01x03 | Connector_PinHeader_2.54mm:PinHeader_1x03_P2.54mm_Vertical | ~
 |  | LS1 | USTransducer | uFinder:USTransducer | uFinder:ULTRASONIC_16MM
 |  | R1 | 0 | Device:R_US | Resistor_SMD:R_0603_1608Metric_Pad0.98x0.95mm_HandSolder | ~ | 311-51.0CRCT-ND | Yageo | RC0805FR-0751RL
 |  | R2 | 0 | Device:R_US | Resistor_SMD:R_0603_1608Metric_Pad0.98x0.95mm_HandSolder | ~ | 311-51.0CRCT-ND | Yageo | RC0805FR-0751RL
 |  | R3 | NP | Device:R_US | Resistor_SMD:R_0603_1608Metric_Pad0.98x0.95mm_HandSolder | ~ | NA | NA | NA
 |  | U1 | 74AHC1G04 | uFinder:74AHC1G04 | Package_TO_SOT_SMD:SOT-353_SC-70-5_Handsoldering | https://www.diodes.com/assets/Datasheets/74AHC1G04.pdf
 |  | U2 | MAX232 | Interface_UART:MAX232 | Package_SO:TSSOP-16_4.4x5mm_P0.65mm | https://www.renesas.com/us/en/document/dst/icl3221-icl3222-i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 | ICL3232IVZ-ND | Renesas | ICL3232IVZ
Collated Components:
 |  |  |  |  |  |  |  |  |  |  | Num Boards | 12
Item | Qty | Reference(s) | Value | LibPart | Footprint | Datasheet | DK PN | MFG | MFG PN | Cost (10+) | Ext Cost | Notes
1 | 5 | C1, C2, C3, C4, C5 | 1u | Device:C | Capacitor_SMD:C_0603_1608Metric_Pad1.08x0.95mm_HandSolder | ~ | 1276-1102-1-ND | Samsung | CL10A105KA8NNNC | 3.4000000000000002E-2 | 2.04
2 | 3 | FID1, FID2, FID3 | Fiducial | Mechanical:Fiducial | Fiducial:Fiducial_1mm_Mask2mm | ~ | NA | NA | NA | 0 | 0
3 | 1 | H1 | GND | Mechanical:MountingHole_Pad | TestPoint:TestPoint_Keystone_5005-5009_Compact | ~ | 36-1041-ND | Keystone | 1041 | 0.26319999999999999 | 3.1583999999999999
4 | 4 | H2, H3, H4, H5 | MountingHole | Mechanical:MountingHole | MountingHole:MountingHole_3.2mm_M3 | ~ | NA | NA | NA | 0 | 0
5 | 1 | J1 | Phoenix 1984620 | Connector:Screw_Terminal_01x03 | Connector_PinHeader_2.54mm:PinHeader_1x03_P2.54mm_Vertical | ~ | 277-1722-ND | Phoenix | 1984620 | 0.78200000000000003 | 9.3840000000000003
6 | 1 | LS1 | USTransducer | uFinder:USTransducer | uFinder:ULTRASONIC_16MM |  |  |  |  |  | 0 | Amazon
7 | 2 | R1, R2 | 0 | Device:R_US | Resistor_SMD:R_0603_1608Metric_Pad0.98x0.95mm_HandSolder | ~ | 311-0.0HRCT-ND | Yageo | RC0603FR-070RL | 1.7999999999999999E-2 | 0.43199999999999994
8 | 1 | R3 | NP | Device:R_US | Resistor_SMD:R_0603_1608Metric_Pad0.98x0.95mm_HandSolder | ~ | NA | NA | NA | 0 | 0
9 | 1 | U1 | 74AHC1G04 | uFinder:74AHC1G04 | Package_TO_SOT_SMD:SOT-353_SC-70-5_Handsoldering | https://www.ti.com/general/docs/suppproductinfo.tsp?distId=1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 | 296-17248-1-ND | TI | SN74AHC1G04QDCKRQ1 | 0.41 | 4.92
10 | 1 | U2 | MAX232 | Interface_UART:MAX232 | Package_SO:TSSOP-16_4.4x5mm_P0.65mm | https://www.renesas.com/us/en/document/dst/icl3221-icl3222-i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 | ICL3232IVZ-ND | Renesas | ICL3232IVZ | 1.8540000000000001 | 22.248000000000001

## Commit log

2023-03-31 First
2023-04-03 added transcievers, basic ping
2023-04-06 added second receiver, state machine
2023-04-07 Copy existing boards into new repo
2023-04-07 New logo graphics
2023-04-07 Update logo on receiver board; add new logo footprint & symbol
2023-04-07 Adjustments to new logo
2023-04-07 pdf of 0.1 receive board
2023-04-07 mcu prototype board r1
2023-04-09 gerbers and few updates
2023-04-09 readme update
2023-04-09 gitignore temp folders
2023-04-10 receiver board v2
2023-04-10 First stage reorganization; adding web server stuff
2023-04-11 Recv V2 layout
2023-04-11 Clean up pours
2023-04-12 routed
2023-04-12 Second try for receive PCB layout
2023-04-13 my board
2023-04-13 move bl's files into elliot's folders
2023-04-13 panelized
2023-04-14 make all current objects singletons
2023-04-14 Address silkscreen DRC
2023-04-14 some autosave file changed
2023-04-14 updated panel
2023-04-14 individual board production outputs
2023-04-17 Got LED, SPIFFS, JSON read, WIFI, and webserver working
2023-04-17 Automatic pairing for ESP-NOW
2023-04-18 Automatic pairing and saving to JSON
2023-04-18 updated todo list
2023-04-19 Deactivate AP without breaking ESP-NOW
2023-04-21 UART output for receiver
2023-04-21 Updated pin and board definition for transmitter
2023-04-28 Add dual license
2023-05-09 Reorganize & clean up repository
2023-05-11 fix missing receive board
2023-05-11 Restore 2 versions of receive board
